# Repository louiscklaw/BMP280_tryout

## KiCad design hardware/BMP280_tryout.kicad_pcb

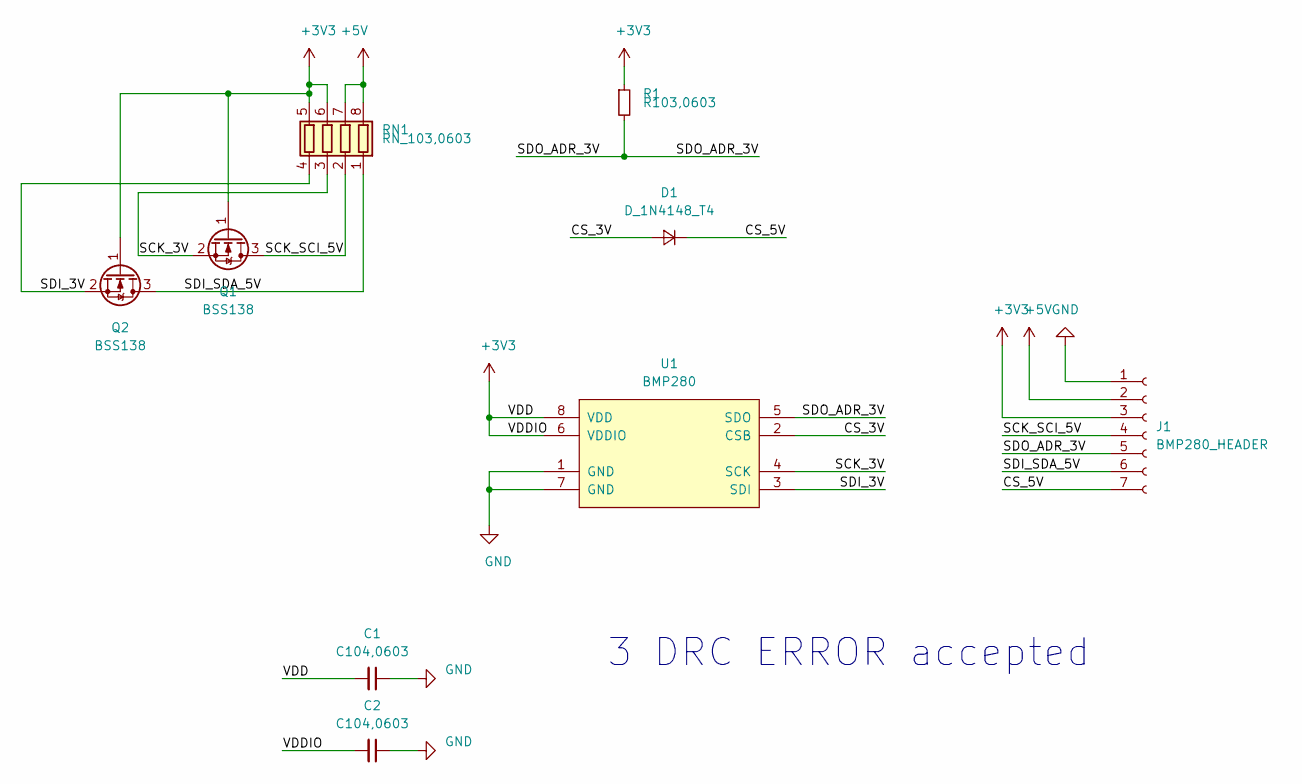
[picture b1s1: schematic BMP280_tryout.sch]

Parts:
C1, C2: C104,0603; C_0603_1608Metric_Pad1.05x0.95mm_HandSolder
D1: D_1N4148_T4; D_SOD-123
J1: BMP280_HEADER; PinHeader_1x07_P1.27mm_Vertical
Q1, Q2: BSS138; SOT-23
R1: R103,0603; R_0603_1608Metric_Pad1.05x0.95mm_HandSolder
RN1: RN_103,0603; R_Array_Concave_4x0603
U1: BMP280

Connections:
+3V3: C1.2, C2.2, J1.3, Q1.1 (G), Q2.1 (G), R1.1, RN1.5 (R4.2), RN1.6 (R3.2), U1.6 (VDDIO), U1.8 (VDD)
+5V: J1.2, RN1.7 (R2.2), RN1.8 (R1.2)
/CS_3V: D1.2 (A), U1.2 (CSB)
/CS_5V: D1.1 (K), J1.7
/SCK_3V: Q1.2 (S), RN1.3 (R3.1), U1.4 (SCK)
/SCK_SCI_5V: J1.4, Q1.3 (D), RN1.2 (R2.1)
/SDI_3V: Q2.2 (S), RN1.4 (R4.1), U1.3 (SDI)
/SDI_SDA_5V: J1.6, Q2.3 (D), RN1.1 (R1.1)
/SDO_ADR_3V: J1.5, R1.2, U1.5 (SDO)
GND: C1.1, C2.1, J1.1, U1.1 (GND), U1.7 (GND)

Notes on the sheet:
3 DRC ERROR accepted

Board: 2 copper layers, 9 parts (3 on the bottom side), 10 nets, no tracks yet.

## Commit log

2019-06-26 init commit,
2019-06-26 update,
2020-05-05 ci: init travis token,
2020-05-05 ci: init travis build config,
